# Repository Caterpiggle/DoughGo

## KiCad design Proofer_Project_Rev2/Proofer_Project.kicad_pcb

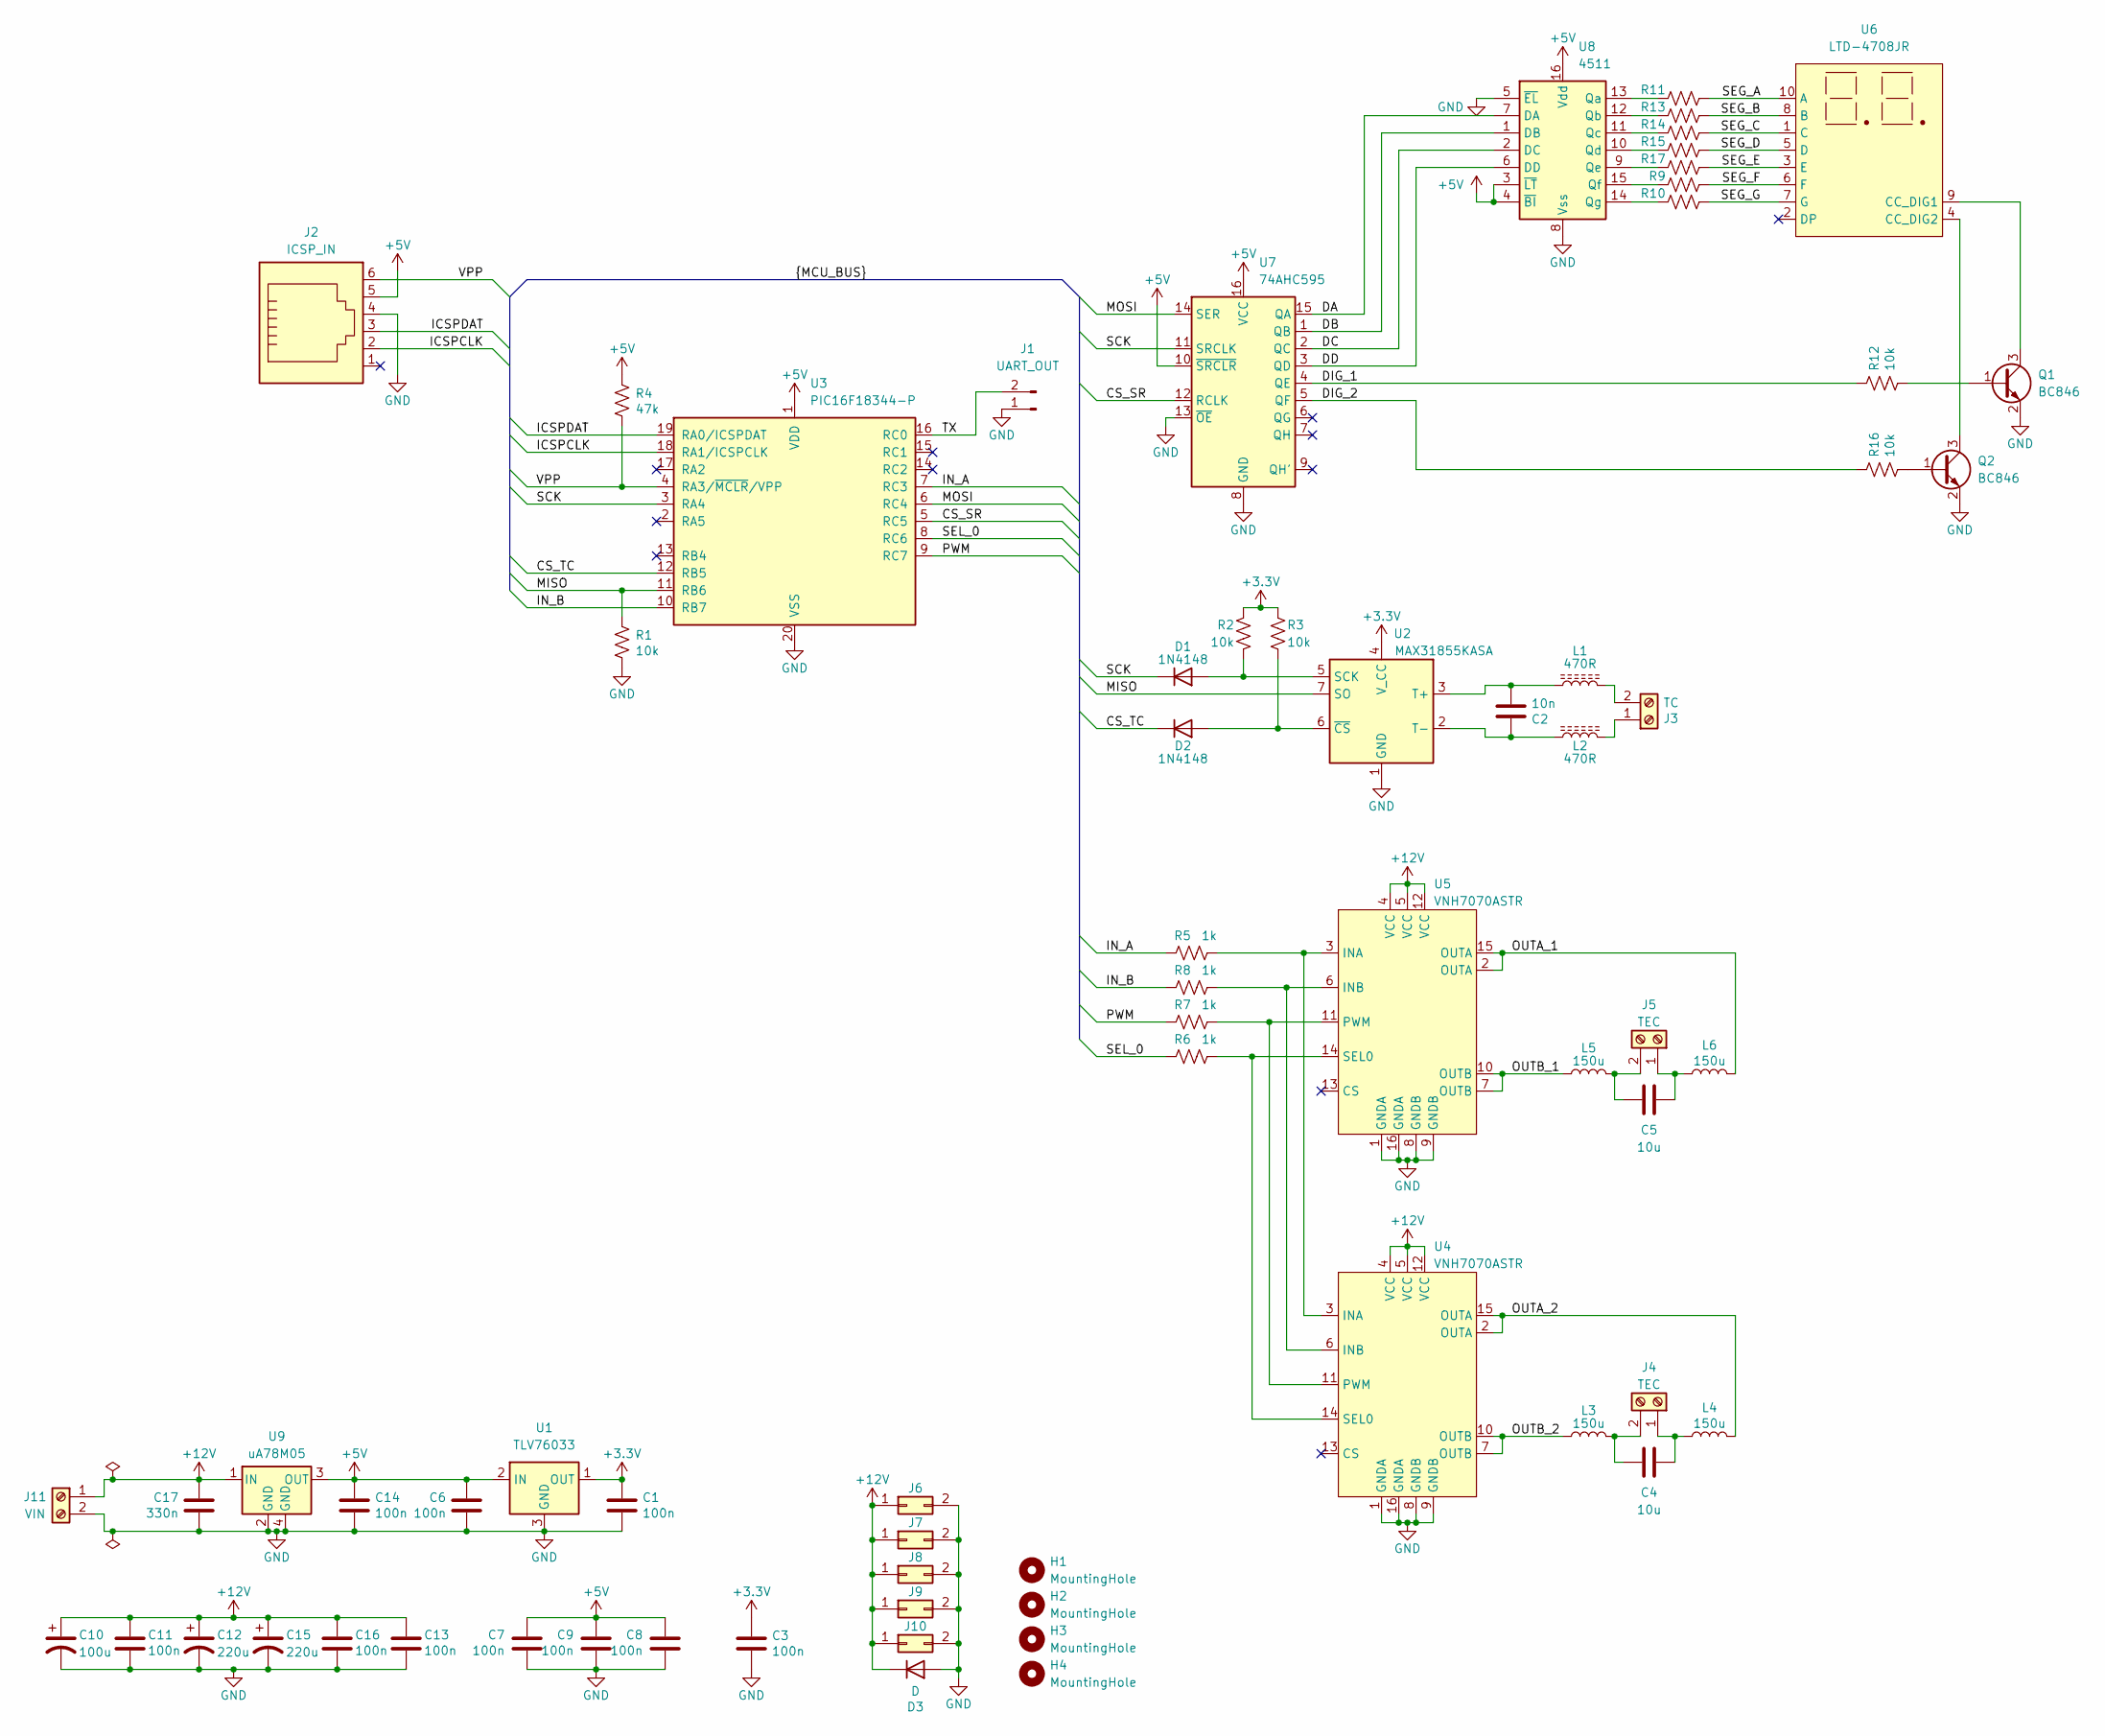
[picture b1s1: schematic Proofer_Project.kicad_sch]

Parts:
C1, C3, C6, C7, C8, C9, C11, C13, C14, C16: 100n; C_0805_2012Metric
C2: 10n; C_0805_2012Metric
C4, C5: 10u; C_Rect_L18.0mm_W9.0mm_P15.00mm_FKS3_FKP3
C10: 100u; CP_Radial_D6.3mm_P2.50mm
C12, C15: 220u; CP_Radial_D6.3mm_P2.50mm
C17: 330n; C_0805_2012Metric
D1, D2: 1N4148; D_SOD-323
D3: D; D_SOD-123
H1, H2, H3, H4: MountingHole; MountingHole_3.2mm_M3
J1: UART_OUT; PinHeader_1x02_P2.54mm_Horizontal
J2: ICSP_IN; RJ11
J3: TC; TerminalBlock_bornier-2_P5.08mm
J4, J5: TEC; TerminalBlock_bornier-2_P5.08mm
J6, J7, J8, J9, J10: Conn_02x01; PinHeader_1x02_P2.54mm_Vertical
J11: VIN; TerminalBlock_bornier-2_P5.08mm
L1, L2: 470R; L_0805_2012Metric
L3, L4, L5, L6: 150u; L_Toroid_Vertical_L26.7mm_W14.0mm_P10.16mm_Pulse_D
Q1, Q2: BC846; SOT-23
R1, R2, R3, R12, R16: 10k; R_0805_2012Metric
R4: 47k; R_0805_2012Metric
R5, R6, R7, R8: 1k; R_0805_2012Metric
R9, R10, R11, R13, R14, R15, R17: R_US; R_0805_2012Metric
U1: TLV76033; SOT-23
U2: MAX31855KASA; SOIC-8_3.9x4.9mm_P1.27mm
U3: PIC16F18344-P; DIP-20_W7.62mm_Socket
U4, U5: VNH7070ASTR; SO-16_3.9x9.9mm_P1.27mm
U6: LTD-4708JR
U7: 74AHC595; SOIC-16_3.9x9.9mm_P1.27mm
U8: 4511; SOIC-16_3.9x9.9mm_P1.27mm
U9: uA78M05; SOT-223

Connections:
+3.3V: C1.1, C3.1, R2.1, R3.1, U1.1 (OUT), U2.4 (V_CC)
+5V: C6.1, C7.1, C8.1, C9.1, C14.1, J2.5, R4.2, U1.2 (IN), U3.1 (VDD), U7.10 (~SRCLR), U7.16 (VCC), U8.3 (~LT), U8.4 (~BI), U8.16 (Vdd), U9.3 (OUT)
+12V: C10.1, C11.1, C12.1, C13.1, C15.1, C16.1, C17.1, D3.1 (K), J6.1, J7.1, J8.1, J9.1, J10.1, J11.1, U4.4 (VCC), U4.5 (VCC), U4.12 (VCC), U5.4 (VCC), U5.5 (VCC), U5.12 (VCC), U9.1 (IN)
/CS_SR: U3.5 (RC5), U7.12 (RCLK)
/CS_TC: D2.1 (K), U3.12 (RB5)
/DA: U7.15 (QA), U8.7 (DA)
/DB: U7.1 (QB), U8.1 (DB)
/DC: U7.2 (QC), U8.2 (DC)
/DD: U7.3 (QD), U8.6 (DD)
/DIG_1: R12.1, U7.4 (QE)
/DIG_2: R16.1, U7.5 (QF)
/ICSPCLK: J2.2, U3.18 (RA1/ICSPCLK)
/ICSPDAT: J2.3, U3.19 (RA0/ICSPDAT)
/IN_A: R5.1, U3.7 (RC3)
/IN_B: R8.1, U3.10 (RB7)
/MISO: R1.2, U2.7 (SO), U3.11 (RB6)
/MOSI: U3.6 (RC4), U7.14 (SER)
/OUTA_1: L6.2, U5.2 (OUTA), U5.15 (OUTA)
/OUTA_2: L4.2, U4.2 (OUTA), U4.15 (OUTA)
/OUTB_1: L5.1, U5.7 (OUTB), U5.10 (OUTB)
/OUTB_2: L3.1, U4.7 (OUTB), U4.10 (OUTB)
/PWM: R7.1, U3.9 (RC7)
/SCK: D1.1 (K), U3.3 (RA4), U7.11 (SRCLK)
/SEG_A: R11.2, U6.10 (A)
/SEG_B: R13.2, U6.8 (B)
/SEG_C: R14.2, U6.1 (C)
/SEG_D: R15.2, U6.5 (D)
/SEG_E: R17.2, U6.3 (E)
/SEG_F: R9.2, U6.6 (F)
/SEG_G: R10.2, U6.7 (G)
/SEL_0: R6.1, U3.8 (RC6)
/TX: J1.2, U3.16 (RC0)
/VPP: J2.6, R4.1, U3.4 (RA3/~MCLR/VPP)
GND: C1.2, C3.2, C6.2, C7.2, C8.2, C9.2, C10.2, C11.2, C12.2, C13.2, C14.2, C15.2, C16.2, C17.2, D3.2 (A), J1.1, J2.4, J6.2, J7.2, J8.2, J9.2, J10.2, J11.2, Q1.2 (E), Q2.2 (E), R1.1, U1.3 (GND), U2.1 (GND), U3.20 (VSS), U4.1 (GNDA), U4.8 (GNDB), U4.9 (GNDB), U4.16 (GNDA), U5.1 (GNDA), U5.8 (GNDB), U5.9 (GNDB), U5.16 (GNDA), U7.8 (GND), U7.13 (~OE), U8.5 (~EL), U8.8 (Vss), U9.2 (GND), U9.4 (GND)
unnamed: D1.2 (A), R2.2, U2.5 (SCK)
unnamed: D2.2 (A), R3.2, U2.6 (~CS)
unnamed: J3.1, L2.2
unnamed: J3.2, L1.2
unnamed: C4.2, J4.1, L4.1
unnamed: C4.1, J4.2, L3.2
unnamed: C5.2, J5.1, L6.1
unnamed: C5.1, J5.2, L5.2
unnamed: Q1.1 (B), R12.2
unnamed: Q1.3 (C), U6.9 (CC_DIG1)
unnamed: Q2.1 (B), R16.2
unnamed: Q2.3 (C), U6.4 (CC_DIG2)
unnamed: C2.2, L1.1, U2.3 (T+)
unnamed: C2.1, L2.1, U2.2 (T-)
unnamed: R5.2, U4.3 (INA), U5.3 (INA)
unnamed: R8.2, U4.6 (INB), U5.6 (INB)
unnamed: R7.2, U4.11 (PWM), U5.11 (PWM)
unnamed: R6.2, U4.14 (SEL0), U5.14 (SEL0)
unnamed: R11.1, U8.13 (Qa)
unnamed: R13.1, U8.12 (Qb)
unnamed: R14.1, U8.11 (Qc)
unnamed: R15.1, U8.10 (Qd)
unnamed: R17.1, U8.9 (Qe)
unnamed: R9.1, U8.15 (Qf)
unnamed: R10.1, U8.14 (Qg)

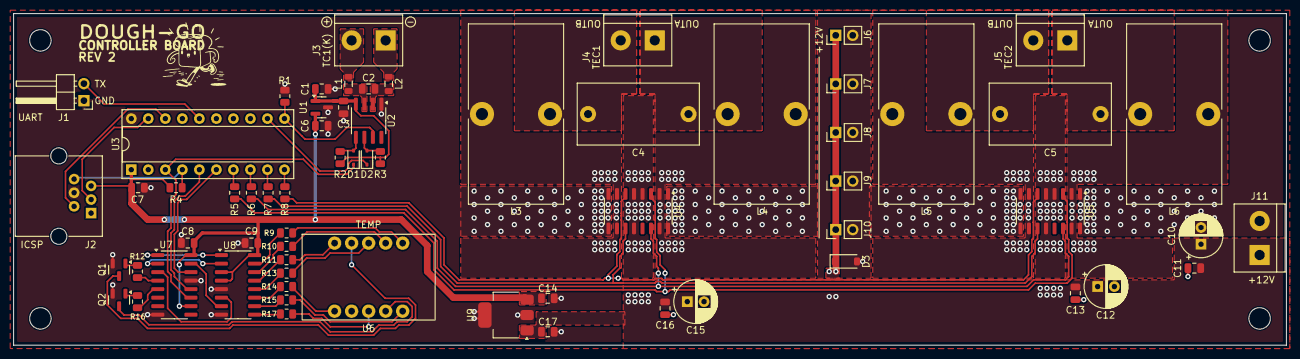
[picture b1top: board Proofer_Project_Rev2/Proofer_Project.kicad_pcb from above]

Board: 2 copper layers, 190.0 x 49.5 mm, 69 parts (0 on the bottom side), 59 nets.

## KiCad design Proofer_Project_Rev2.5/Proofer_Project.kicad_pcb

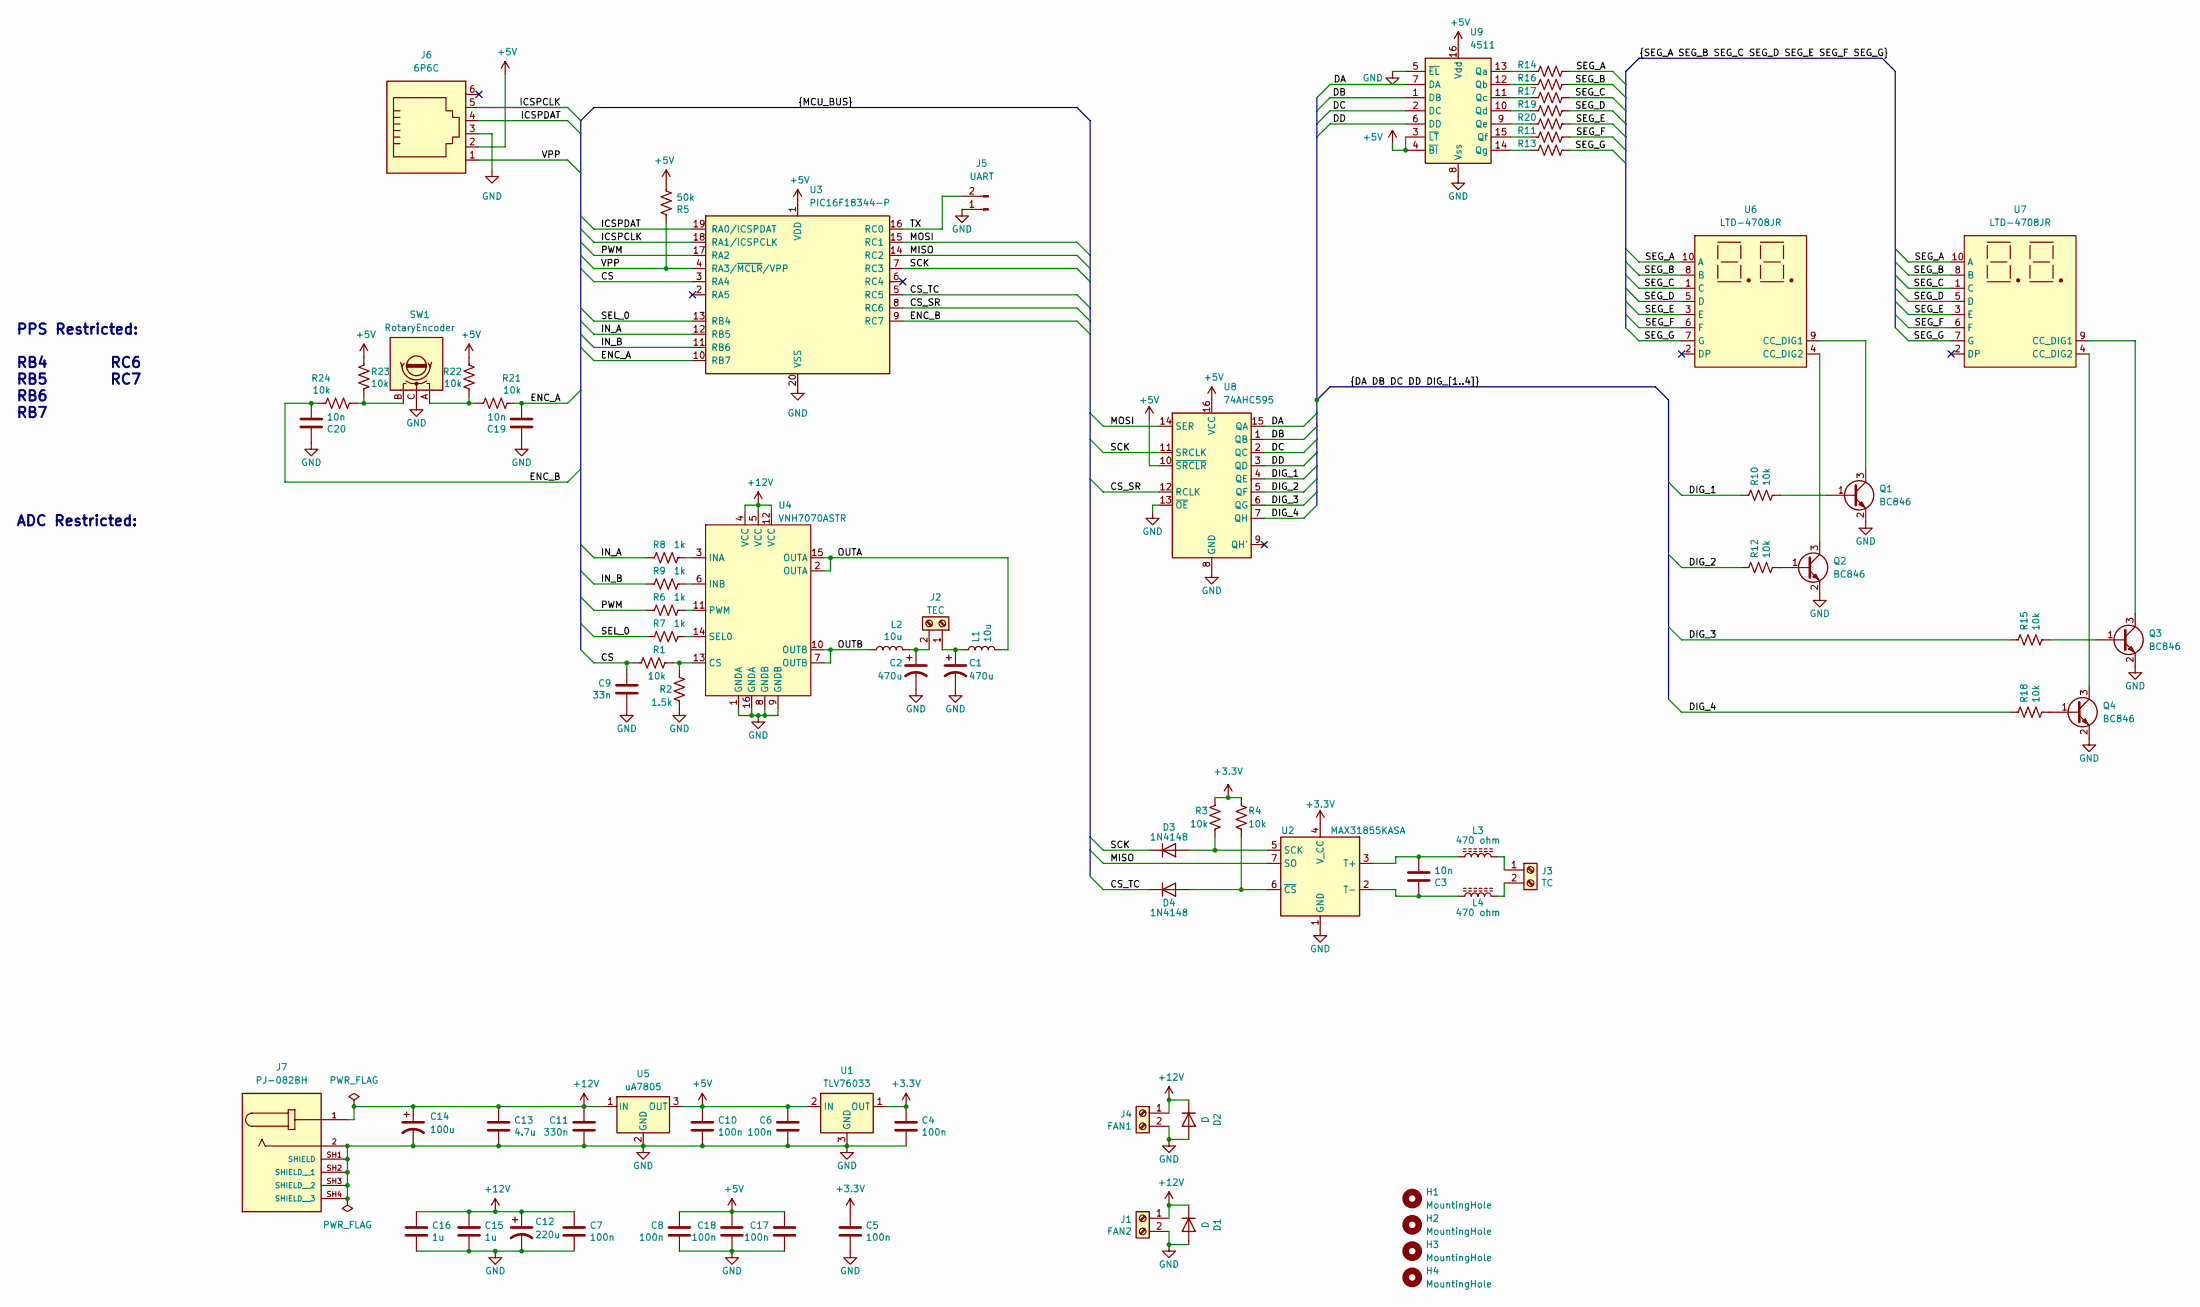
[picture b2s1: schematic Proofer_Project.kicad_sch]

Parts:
C1, C2: 470u; CP_Radial_D10.0mm_P5.00mm
C3, C19, C20: 10n; C_0805_2012Metric
C4, C5, C6, C7, C8, C10, C17, C18: 100n; C_0805_2012Metric
C9: 33n; C_0805_2012Metric
C11: 330n; C_0805_2012Metric
C12: 220u; CP_Radial_D5.0mm_P2.00mm
C13: 4.7u; C_0805_2012Metric
C14: 100u; CP_Radial_D5.0mm_P2.00mm
C15, C16: 1u; C_0805_2012Metric
D1, D2: D; D_SOD-123
D3, D4: 1N4148; D_SOD-323
H1, H2, H3, H4: MountingHole; MountingHole_3.2mm_M3
J1: FAN2; TerminalBlock_bornier-2_P5.08mm
J2: TEC; TerminalBlock_bornier-2_P5.08mm
J3: TC; PCC-SMP
J4: FAN1; TerminalBlock_bornier-2_P5.08mm
J5: UART; PinHeader_1x02_P2.54mm_Horizontal
J6: 6P6C; RJ11
J7: PJ-082BH; CUI_PJ-082BH; PARTREV 1.04
L1, L2: 10u; L_Radial_D24.4mm_P23.90mm_Murata_1400series
L3, L4: 470 ohm; L_0805_2012Metric
Q1, Q2, Q3, Q4: BC846; SOT-23
R1, R3, R4, R10, R12, R15, R18, R21, R22, R23, R24: 10k; R_0805_2012Metric
R2: 1.5k; R_0805_2012Metric
R5: 50k; R_0805_2012Metric
R6, R7, R8, R9: 1k; R_0805_2012Metric
R11, R13, R14, R16, R17, R19, R20: R_US; R_0805_2012Metric
SW1: RotaryEncoder; RotaryEncoder_Alps_EC11E-Switch_Vertical_H20mm
U1: TLV76033; SOT-23
U2: MAX31855KASA; SOIC-8_3.9x4.9mm_P1.27mm
U3: PIC16F18344-P; DIP-20_W7.62mm_Socket
U4: VNH7070ASTR; SO-16_3.9x9.9mm_P1.27mm
U5: uA7805; SOT-223
U6, U7: LTD-4708JR
U8: 74AHC595; SOIC-16_3.9x9.9mm_P1.27mm
U9: 4511; SOIC-16_3.9x9.9mm_P1.27mm

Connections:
+3.3V: C4.1, C5.1, R3.1, R4.1, U1.1 (OUT), U2.4 (V_CC)
+5V: C6.1, C8.1, C10.1, C17.1, C18.1, J6.2, R5.2, R22.2, R23.2, U1.2 (IN), U3.1 (VDD), U5.3 (OUT), U8.10 (~SRCLR), U8.16 (VCC), U9.3 (~LT), U9.4 (~BI), U9.16 (Vdd)
+12V: C7.1, C11.1, C12.1, C13.1, C14.1, C15.1, C16.1, D1.1 (K), D2.1 (K), J1.1, J4.1, J7.1, U4.4 (VCC), U4.5 (VCC), U4.12 (VCC), U5.1 (IN)
/CS: C9.1, R1.1, U3.3 (RA4)
/CS_SR: U3.8 (RC6), U8.12 (RCLK)
/CS_TC: D4.1 (K), U3.5 (RC5)
/DA: U8.15 (QA), U9.7 (DA)
/DB: U8.1 (QB), U9.1 (DB)
/DC: U8.2 (QC), U9.2 (DC)
/DD: U8.3 (QD), U9.6 (DD)
/DIG_1: R10.1, U8.4 (QE)
/DIG_2: R12.1, U8.5 (QF)
/DIG_3: R15.1, U8.6 (QG)
/DIG_4: R18.1, U8.7 (QH)
/ENC_A: C19.2, R21.2, U3.10 (RB7)
/ENC_B: C20.2, R24.1, U3.9 (RC7)
/ICSPCLK: J6.5, U3.18 (RA1/ICSPCLK)
/ICSPDAT: J6.4, U3.19 (RA0/ICSPDAT)
/IN_A: R8.1, U3.12 (RB5)
/IN_B: R9.1, U3.11 (RB6)
/MISO: U2.7 (SO), U3.14 (RC2)
/MOSI: U3.15 (RC1), U8.14 (SER)
/OUTA: L1.2, U4.2 (OUTA), U4.15 (OUTA)
/OUTB: L2.1, U4.7 (OUTB), U4.10 (OUTB)
/PWM: R6.1, U3.17 (RA2)
/SCK: D3.1 (K), U3.7 (RC3), U8.11 (SRCLK)
/SEG_A: R14.2, U6.10 (A), U7.10 (A)
/SEG_B: R16.2, U6.8 (B), U7.8 (B)
/SEG_C: R17.2, U6.1 (C), U7.1 (C)
/SEG_D: R19.2, U6.5 (D), U7.5 (D)
/SEG_E: R20.2, U6.3 (E), U7.3 (E)
/SEG_F: R11.2, U6.6 (F), U7.6 (F)
/SEG_G: R13.2, U6.7 (G), U7.7 (G)
/SEL_0: R7.1, U3.13 (RB4)
/TX: J5.2, U3.16 (RC0)
/VPP: J6.1, R5.1, U3.4 (RA3/~MCLR/VPP)
GND: C1.2, C2.2, C4.2, C5.2, C6.2, C7.2, C8.2, C9.2, C10.2, C11.2, C12.2, C13.2, C14.2, C15.2, C16.2, C17.2, C18.2, C19.1, C20.1, D1.2 (A), D2.2 (A), J1.2, J4.2, J5.1, J6.3, J7.2, J7.SH1 (SHIELD), J7.SH2 (SHIELD__1), J7.SH3 (SHIELD__2), J7.SH4 (SHIELD__3), Q1.2 (E), Q2.2 (E), Q3.2 (E), Q4.2 (E), R2.1, SW1.C, U1.3 (GND), U2.1 (GND), U3.20 (VSS), U4.1 (GNDA), U4.8 (GNDB), U4.9 (GNDB), U4.16 (GNDA), U5.2 (GND), U8.8 (GND), U8.13 (~OE), U9.5 (~EL), U9.8 (Vss)
unnamed: D3.2 (A), R3.2, U2.5 (SCK)
unnamed: D4.2 (A), R4.2, U2.6 (~CS)
unnamed: C1.1, J2.1, L1.1
unnamed: C2.1, J2.2, L2.2
unnamed: J3.1, L3.2
unnamed: J3.2, L4.2
unnamed: Q1.1 (B), R10.2
unnamed: Q1.3 (C), U6.9 (CC_DIG1)
unnamed: Q2.1 (B), R12.2
unnamed: Q2.3 (C), U6.4 (CC_DIG2)
unnamed: Q3.1 (B), R15.2
unnamed: Q3.3 (C), U7.9 (CC_DIG1)
unnamed: Q4.1 (B), R18.2
unnamed: Q4.3 (C), U7.4 (CC_DIG2)
unnamed: R21.1, R22.1, SW1.A
unnamed: R23.1, R24.2, SW1.B
unnamed: C3.2, L3.1, U2.3 (T+)
unnamed: C3.1, L4.1, U2.2 (T-)
unnamed: R1.2, R2.2, U4.13 (CS)
unnamed: R8.2, U4.3 (INA)
unnamed: R9.2, U4.6 (INB)
unnamed: R6.2, U4.11 (PWM)
unnamed: R7.2, U4.14 (SEL0)
unnamed: R14.1, U9.13 (Qa)
unnamed: R16.1, U9.12 (Qb)
unnamed: R17.1, U9.11 (Qc)
unnamed: R19.1, U9.10 (Qd)
unnamed: R20.1, U9.9 (Qe)
unnamed: R11.1, U9.15 (Qf)
unnamed: R13.1, U9.14 (Qg)

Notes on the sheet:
ADC Restricted:
PPS Restricted: RB4 RC6 RB5 RC7 RB6 RB7

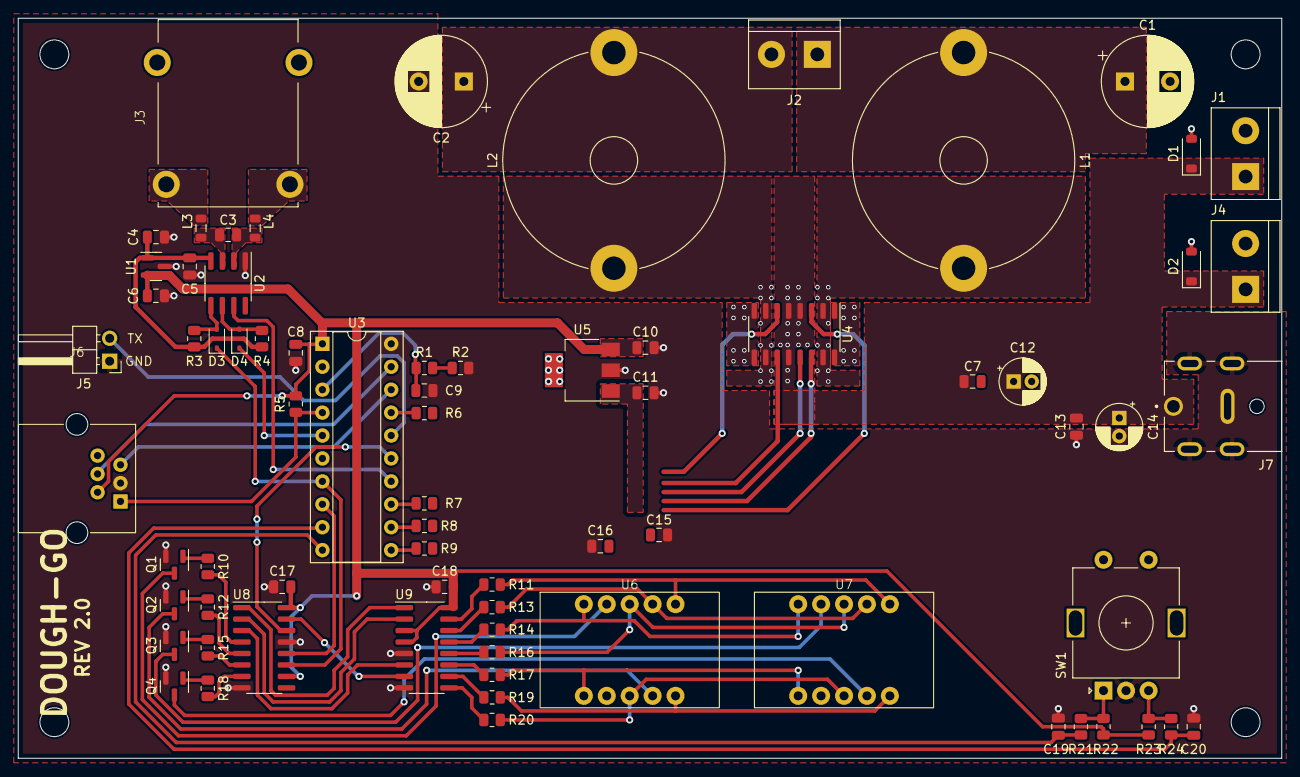
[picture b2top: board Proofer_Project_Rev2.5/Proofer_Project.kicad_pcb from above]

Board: 2 copper layers, 140.0 x 82.0 mm, 77 parts (0 on the bottom side), 67 nets.

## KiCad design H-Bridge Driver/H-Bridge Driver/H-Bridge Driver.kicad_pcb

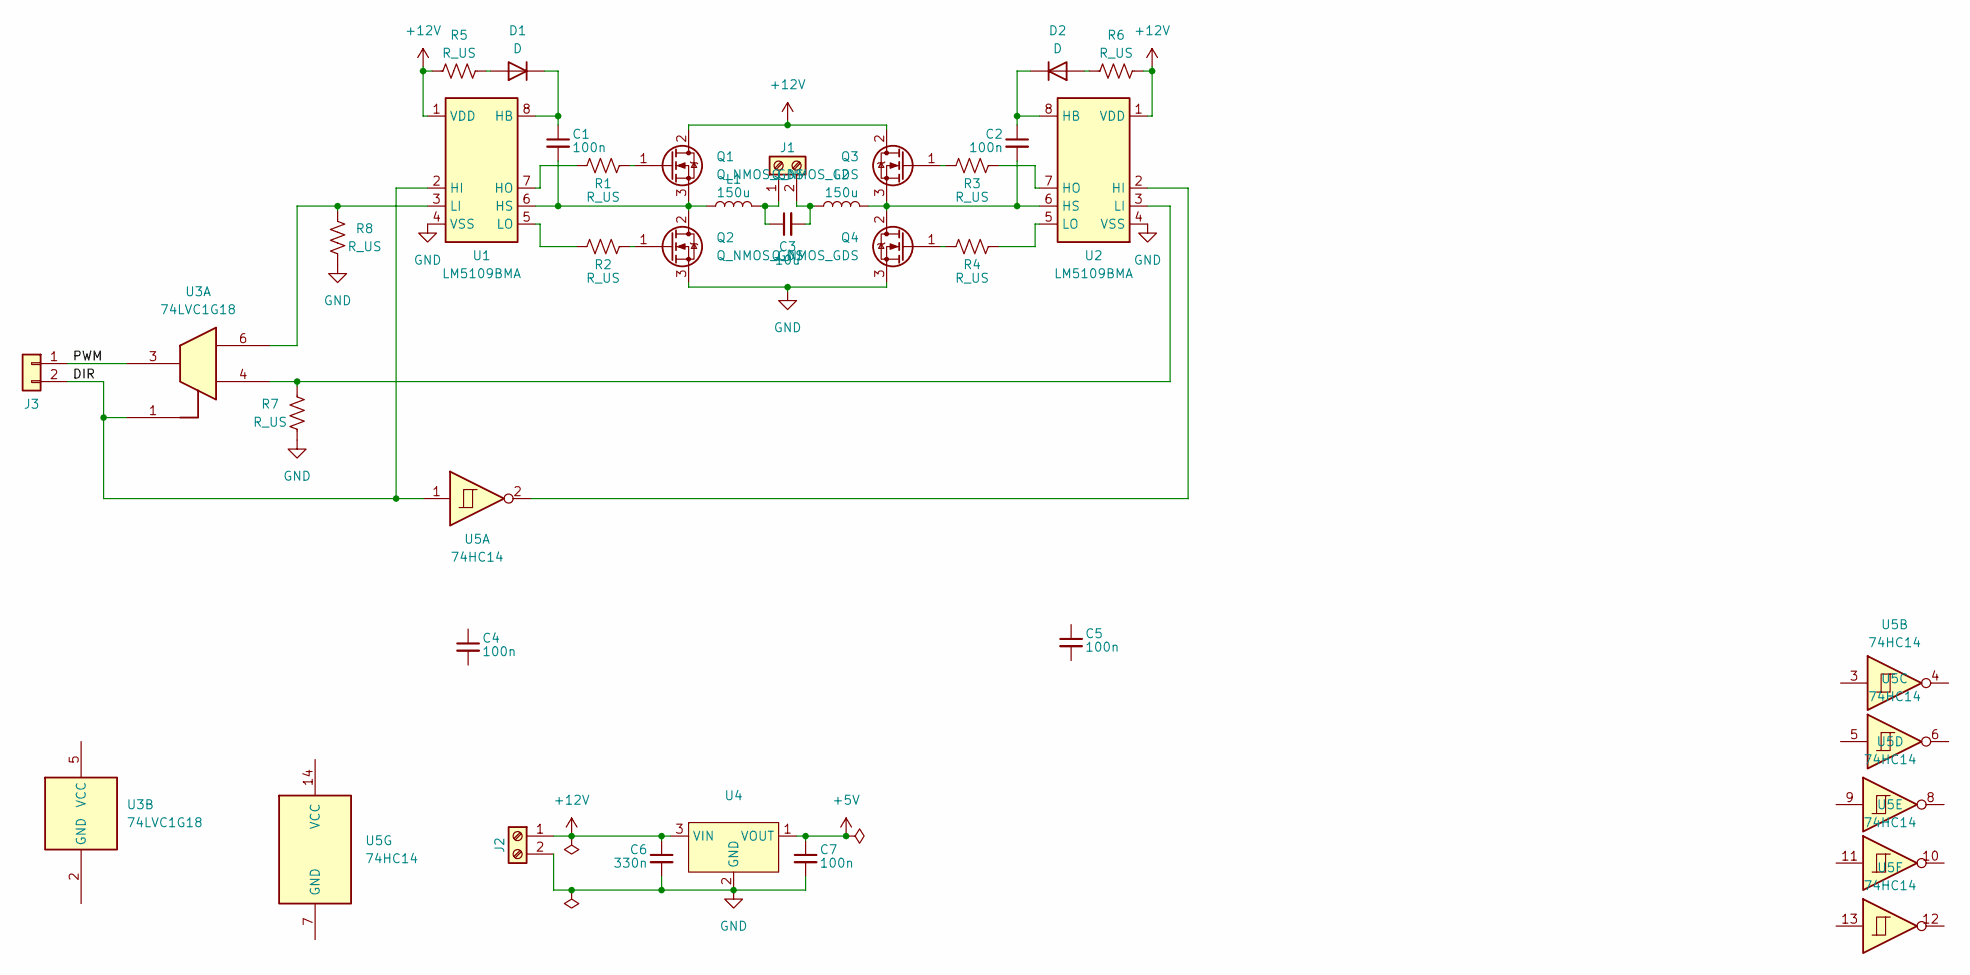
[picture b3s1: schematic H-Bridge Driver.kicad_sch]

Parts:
C1, C2, C4, C5, C7: 100n; C_0805_2012Metric
C3: 10u; C_Rect_L18.0mm_W9.0mm_P15.00mm_FKS3_FKP3
C6: 330n; C_0805_2012Metric
D1, D2: D; D_SOD-323
J1, J2: Screw_Terminal_01x02; TerminalBlock_bornier-2_P5.08mm
J3: Conn_01x02; PinHeader_1x02_P2.54mm_Vertical
L1, L2: 150u; L_Toroid_Vertical_L26.7mm_W14.0mm_P10.16mm_Pulse_D
Q1, Q2, Q3, Q4: Q_NMOS_GDS; TO-252-2
R1, R2, R3, R4, R5, R6, R7, R8: R_US; R_0805_2012Metric
U1, U2: LM5109BMA; SOIC-8_3.9x4.9mm_P1.27mm
U3: 74LVC1G18; SOT-23-6
U4: SOT-89-3
U5: 74HC14

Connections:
+5V: C7.1, U4.1 (VOUT)
+12V: C6.1, J2.1, Q1.2 (D), Q3.2 (D), R5.1, R6.2, U1.1 (VDD), U2.1 (VDD), U4.3 (VIN)
/DIR: J3.2, U1.2 (HI), U3.1, U5.1
/PWM: J3.1, U3.3
GND: C6.2, C7.2, J2.2, Q2.3 (S), Q4.3 (S), R7.1, R8.1, U1.4 (VSS), U2.4 (VSS), U4.2 (GND)
unnamed: D1.2 (A), R5.2
unnamed: C1.1, D1.1 (K), U1.8 (HB)
unnamed: D2.2 (A), R6.1
unnamed: C2.1, D2.1 (K), U2.8 (HB)
unnamed: C3.1, J1.1, L1.2
unnamed: C3.2, J1.2, L2.1
unnamed: Q1.1 (G), R1.2
unnamed: C1.2, L1.1, Q1.3 (S), Q2.2 (D), U1.6 (HS)
unnamed: Q2.1 (G), R2.2
unnamed: Q3.1 (G), R3.1
unnamed: C2.2, L2.2, Q3.3 (S), Q4.2 (D), U2.6 (HS)
unnamed: Q4.1 (G), R4.1
unnamed: R1.1, U1.7 (HO)
unnamed: R8.2, U1.3 (LI), U3.6
unnamed: R2.1, U1.5 (LO)
unnamed: U2.2 (HI), U5.2
unnamed: R3.2, U2.7 (HO)
unnamed: R7.2, U2.3 (LI), U3.4
unnamed: R4.2, U2.5 (LO)

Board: 2 copper layers, 30 parts (0 on the bottom side), 23 nets, no tracks yet.

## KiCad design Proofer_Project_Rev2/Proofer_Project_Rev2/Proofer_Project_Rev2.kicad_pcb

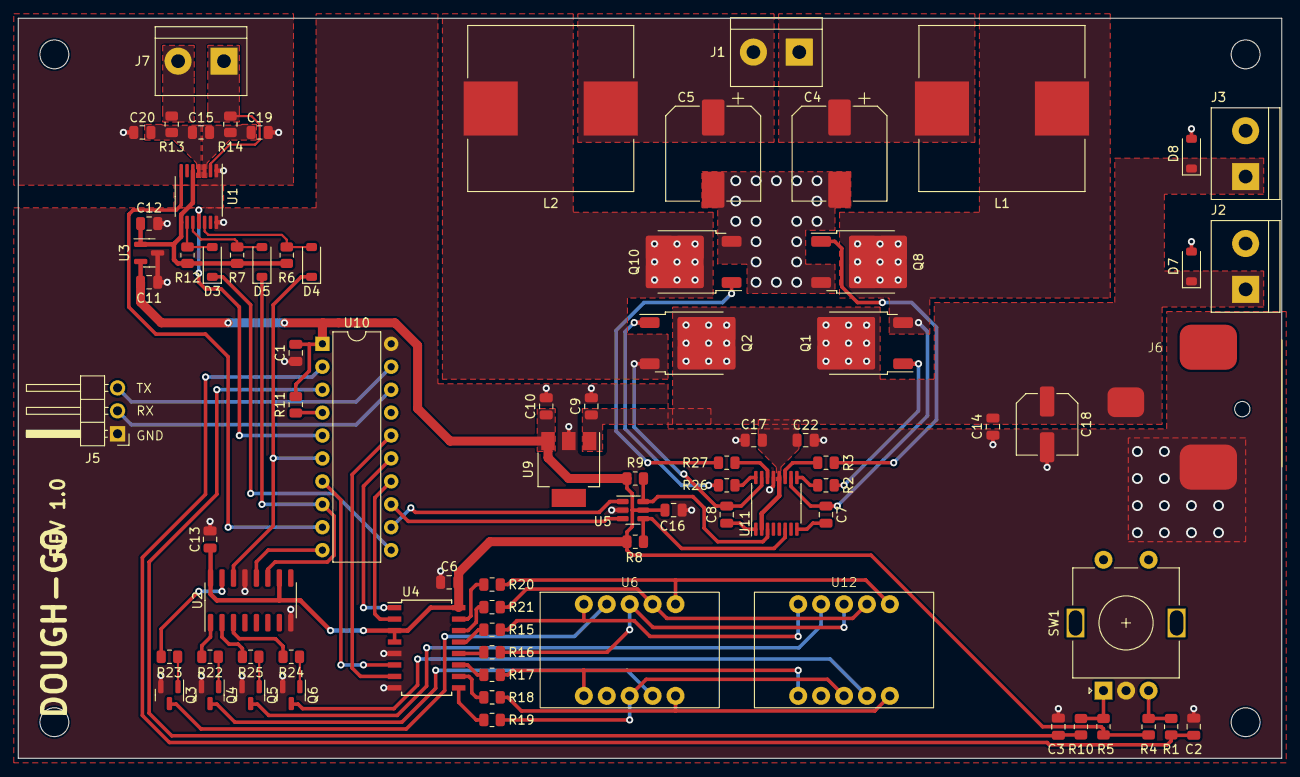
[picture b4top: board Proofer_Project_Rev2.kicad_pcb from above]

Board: 2 copper layers, 140.0 x 82.0 mm, 84 parts (0 on the bottom side), 72 nets.

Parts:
C1, C6, C10, C11, C12, C13, C15, C16: 100n; C_0805_2012Metric
C2, C3, C19, C20: 10n; C_0805_2012Metric
C4, C5: 470u; CP_Elec_10x10
C7, C8, C17, C22: 1u; C_0805_2012Metric
C9: 330n; C_0805_2012Metric
C14: 4.7u; C_0805_2012Metric
C18: 100u; C_Elec_6.3x5.4
D3, D4, D5, D7, D8: D; D_SOD-123
H1, H2, H3, H4: MountingHole; MountingHole_3.2mm_M3
J1: TEC; TerminalBlock_bornier-2_P5.08mm
J2: FAN1; TerminalBlock_bornier-2_P5.08mm
J3: FAN2; TerminalBlock_bornier-2_P5.08mm
J5: UART; PinHeader_1x03_P2.54mm_Horizontal
J6: Barrel_Jack_Switch; RASM10PS
J7: TC; TerminalBlock_bornier-2_P5.08mm
L1, L2: 10u; L_Wuerth_HCI-1890
Q1, Q2, Q8, Q10: Q_NMOS_GDS; TO-252-2
Q3, Q4, Q5, Q6: BC846; SOT-23
R1, R4, R5, R6, R7, R8, R9, R10, R11, R12, R22, R23, R24, R25: 10k; R_0805_2012Metric
R2, R26: 10R; R_0805_2012Metric
R3, R27: 2R; R_0805_2012Metric
R13, R14: 100R; R_0805_2012Metric
R15, R16, R17, R18, R19, R20, R21: R_US; R_0805_2012Metric
SW1: Rotary_Encoder; RotaryEncoder_Alps_EC11E-Switch_Vertical_H20mm
U1: MAX31856; TSSOP-14_4.4x5mm_P0.65mm
U2: 74AHC595; SOIC-16_3.9x9.9mm_P1.27mm
U3: TLV76033; SOT-23
U4: 4511; SOIC-16W_5.3x10.2mm_P1.27mm
U5: 74LVC1G18; SOT-23-6
U6, U12: LTD-4708JR
U9: uA7805; SOT-223
U10: PIC16F18344-P; DIP-20_W7.62mm
U11: MIC4606-2; TSSOP-16_4.4x5mm_P0.65mm

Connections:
+3.3V: C12.1, R6.1, R7.1, R12.1, U1.5 (AVDD), U1.8 (DVDD), U3.1 (OUT)
+5V: C1.1, C6.1, C10.1, C11.1, C13.1, C16.1, R4.2, R5.2, R8.2, R9.1, R11.2, U2.10 (~SRCLR), U2.16 (VCC), U3.2 (IN), U4.3 (~LT), U4.4 (~BI), U4.16 (Vdd), U5.5 (VCC), U9.3 (OUT), U10.1 (VDD)
+12V: C9.1, C14.1, C17.1, C18.1, C22.1, D7.1 (K), D8.1 (K), J2.1, J3.1, J6.1, Q1.2 (D), Q2.2 (D), U9.1 (IN), U11.2 (EN), U11.12 (VDD)
/CS_SR: U2.12 (RCLK), U10.10 (RB7)
/CS_TC: D3.1 (K), U10.11 (RB6)
/DEC_A: U4.7 (DA), U10.16 (RC0)
/DEC_B: U4.1 (DB), U10.15 (RC1)
/DEC_C: U4.2 (DC), U10.14 (RC2)
/DEC_D: U4.6 (DD), U10.7 (RC3)
/DIR_SEL: U5.1, U10.12 (RB5)
/DRDY: U1.7 (~DRDY), U10.9 (RC7)
/ENC_A: C3.2, R10.2, U10.3 (RA4)
/ENC_B: C2.2, R1.1, U10.2 (RA5)
/MISO: U1.11 (SDO), U10.5 (RC5)
/MOSI: D4.1 (K), U2.14 (SER), U10.6 (RC4)
/PWM: U5.3, U10.13 (RB4)
/RX: J5.2, U10.18 (RA1/ICSPCLK)
/SCK: D5.1 (K), U2.11 (SRCLK), U10.8 (RC6)
/TX: J5.3, U10.19 (RA0/ICSPDAT)
GNDA: C1.2, C2.1, C3.1, C4.2, C5.2, C6.2, C9.2, C10.2, C11.2, C12.2, C13.2, C14.2, C16.2, C17.2, C18.2, C19.1, C20.1, C22.2, D7.2 (A), D8.2 (A), J2.2, J3.2, J5.1, J6.2, Q3.2 (E), Q4.2 (E), Q5.2 (E), Q6.2 (E), Q8.3 (S), Q10.3 (S), SW1.C, U1.1 (AGND), U1.14 (DGND), U2.8 (GND), U2.13 (~OE), U3.3 (GND), U4.5 (~EL), U4.8 (Vss), U5.2 (GND), U9.2 (GND), U10.20 (VSS), U11.13 (VSS)
unnamed: D3.2 (A), R12.2, U1.9 (~CS)
unnamed: D4.2 (A), R6.2, U1.12 (SDI)
unnamed: D5.2 (A), R7.2, U1.10 (SCK)
unnamed: C4.1, J1.1, L1.2
unnamed: C5.1, J1.2, L2.1
unnamed: J7.1, R14.1, U1.2 (BIAS)
unnamed: J7.2, R13.1
unnamed: Q1.1 (G), R2.2
unnamed: C7.1, L1.1, Q1.3 (S), Q8.2 (D), U11.10 (AHS)
unnamed: Q2.1 (G), R26.1
unnamed: Q3.1 (B), R23.2
unnamed: Q3.3 (C), U6.9 (CC_DIG1)
unnamed: Q4.1 (B), R22.2
unnamed: Q4.3 (C), U6.4 (CC_DIG2)
unnamed: Q5.1 (B), R25.2
unnamed: Q5.3 (C), U12.9 (CC_DIG1)
unnamed: Q6.1 (B), R24.2
unnamed: Q6.3 (C), U12.4 (CC_DIG2)
unnamed: Q8.1 (G), R3.2
unnamed: C8.2, L2.2, Q2.3 (S), Q10.2 (D), U11.15 (BHS)
unnamed: Q10.1 (G), R27.1
unnamed: R1.2, R4.1, SW1.B
unnamed: R5.1, R10.1, SW1.A
unnamed: C15.2, C20.2, R13.2, U1.4 (T+)
unnamed: C15.1, C19.2, R14.2, U1.3 (T-)
unnamed: R23.1, U2.15 (QA)
unnamed: R22.1, U2.1 (QB)
unnamed: R25.1, U2.2 (QC)
unnamed: R24.1, U2.3 (QD)
unnamed: R15.1, U4.13 (Qa)
unnamed: R16.1, U4.12 (Qb)
unnamed: R17.1, U4.11 (Qc)
unnamed: R18.1, U4.10 (Qd)
unnamed: R19.1, U4.9 (Qe)
unnamed: R20.1, U4.15 (Qf)
unnamed: R21.1, U4.14 (Qg)
unnamed: R11.1, U10.4 (RA3/~MCLR/VPP)
unnamed: C7.2, U11.8 (AHB)
unnamed: R2.1, U11.9 (AHO)
unnamed: R3.1, U11.11 (ALO)
unnamed: R8.1, U5.4, U11.6 (APWM)
unnamed: C8.1, U11.1 (BHB)
unnamed: R26.2, U11.16 (BHO)
unnamed: R27.2, U11.14 (BLO)
unnamed: R9.2, U5.6, U11.3 (BPWM)
unnamed: R15.2, U6.10 (A), U12.10 (A)
unnamed: R16.2, U6.8 (B), U12.8 (B)
unnamed: R17.2, U6.1 (C), U12.1 (C)
unnamed: R18.2, U6.5 (D), U12.5 (D)
unnamed: R19.2, U6.3 (E), U12.3 (E)
unnamed: R20.2, U6.6 (F), U12.6 (F)
unnamed: R21.2, U6.7 (G), U12.7 (G)

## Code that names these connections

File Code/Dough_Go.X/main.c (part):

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#pragma config FCMEN = ON       // Fail-Safe Clock Monitor Enable (Fail-Safe Clock Monitor is enabled)

// CONFIG2
#pragma config MCLRE = ON       // Master Clear Enable bit (MCLR/VPP pin function is MCLR; Weak pull-up enabled)
#pragma config PWRTE = OFF      // Power-up Timer Enable bit (PWRT disabled)
#pragma config WDTE = OFF       // Watchdog Timer Enable bits (WDT disabled; SWDTEN is ignored)
#pragma config LPBOREN = OFF    // Low-power BOR enable bit (ULPBOR disabled)
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#pragma config CPD = OFF        // Data NVM Memory Code Protection bit (Data NVM code protection disabled)

// Pin Definitions
#define	TX  	PORTAbits.RA0   // UART TX output
#define	RX  	PORTAbits.RA1   // UART RX input
#define	ENC_A	PORTAbits.RA4   // Encoder A input
#define	ENC_B	PORTAbits.RA5   // Encoder B input

#define PWM     PORTBbits.RB4   // Peltier driver PWM output
#define DIR_SEL PORTBbits.RB5   // Peltier driver direction selection output
#define CS_TC   PORTBbits.RB6   // Thermocouple chip select output
#define RCLK    PORTBbits.RB7   // Shift register latch output

#define DEC_A   PORTCbits.RC0   // Display decoder bit 0 output
#define DEC_B   PORTCbits.RC1   // Display decoder bit 1 output
#define DEC_C   PORTCbits.RC2   // Display decoder bit 2 output
#define DEC_D   PORTCbits.RC3   // Display decoder bit 3 output
#define MOSI    PORTCbits.RC4   // SPI MOSI output
#define MISO    PORTCbits.RC5   // SPI MISO input
#define SCK     PORTCbits.RC6   // SPI clock output
#define DRDY    PORTCbits.RC7   // TC Data ready input

#define T_MAX   85
#define T_MIN   70
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    uint8_t TC_MB;
    uint8_t TC_LB;
    
    CS_TC = 0;
    TC_HB = SPI_read(0x0C); // LTCBH=
    CS_TC = 1;
    
    CS_TC = 0;
    TC_MB = SPI_read(0x0D); // LTCBH
    CS_TC = 1;
    
    
    CS_TC = 0;
    TC_LB = SPI_read(0x0E); // LTCBH
    CS_TC = 1;
    
    //int temp = ((TC_HB << 16) + (TC_MB << 8) + TC_LB)*1600/6553600;
    T_cur = TC_MB;
}

void get_cur_temp(void) {
    CS_TC = 0;
    SPI_out(0x00);  // CR0
    SPI_out(0x40);  // Set 1SHOT bit
    CS_TC = 1;      // Trigger conversion
    
    while (DRDY);
    
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
    // Initiate ports
    PORTA = 0x00;
    PORTB = 0x40; // RB6 = 1
    PORTC = 0x00;
    
    // Clear data latches
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    //IOCAPbits.IOCAP5 = 1;
    
    // Setup TC converter IC
    //CS_TC = 0;
    //SPI_out(0x80);  // Write - CR0
    //SPI_out(0x80);  // CR0 value
    //CS_TC = 1;
    
    //CS_TC = 0;
    
    //while (1) {
    //    char_print(SPI_read(0x00));
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    
    RCLK  = 0;
    
    PORTCbits.RC0 = 0;	
    PORTCbits.RC1 = 0;	
    PORTCbits.RC2 = 0;	
    PORTCbits.RC3 = 0;
    
    // Enable interrupts
    PIE0bits.IOCIE  = 1;
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
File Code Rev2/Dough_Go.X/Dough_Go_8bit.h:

//=====================================================
//
// Dough-Go Rev 2
// 2024
//
// PIC16F18344
//
//              -----------------
//      VDD  --|  1           20 |--  VSS
//        x  --|  2/RA5   RA0/19 |--  ICSPDAT
//      SCK  --|  3/RA4   RA1/18 |--  ICSPCLK
//      VPP  --|  4/RA3   RA2/17 |--  x
//    CS_SR  --|  5/RC5   RC0/16 |--  UART TX
//     MOSI  --|  6/RC4   RC1/15 |--  x
//     IN_A  --|  7/RC3   RC2/14 |--  X
//    SEL_0  --|  8/RC6   RB4/13 |--  x
//      PWM  --|  9/RC7   RB5/12 |--  CS_TC
//     IN_B  --| 10/RB7   RB6/11 |--  MISO
//              -----------------
//
//=====================================================

// This is a guard condition so that contents of this file are not included
// more than once.  
#ifndef DOUGH_GO_8BIT_H
#define	DOUGH_GO_8BIT_H

#include <xc.h> // include processor files - each processor file is guarded.  
#include <stdint.h>


// CONFIG1
#pragma config FEXTOSC  = OFF     // FEXTOSC External Oscillator mode Selection bits (Oscillator not enabled)
#pragma config RSTOSC   = HFINT1  // Power-up default value for COSC bits (HFINTOSC (1MHz)
#pragma config CLKOUTEN = OFF     // Clock Out Enable bit (CLKOUT function is disabled; I/O or oscillator function on OSC2)
#pragma config CSWEN    = ON      // Clock Switch Enable bit (Writing to NOSC and NDIV is allowed)
#pragma config FCMEN    = ON      // Fail-Safe Clock Monitor Enable (Fail-Safe Clock Monitor is enabled)

// CONFIG2
#pragma config MCLRE    = ON      // Master Clear Enable bit (MCLR/VPP pin function is MCLR; Weak pull-up enabled)
#pragma config PWRTE    = OFF     // Power-up Timer Enable bit (PWRT disabled)
#pragma config WDTE     = OFF     // Watchdog Timer Enable bits (WDT disabled; SWDTEN is ignored)
#pragma config LPBOREN  = OFF     // Low-power BOR enable bit (ULPBOR disabled)
#pragma config BOREN    = OFF     // Brown-out Reset Enable bits (Brown-out Reset disabled)
#pragma config BORV     = LOW     // Brown-out Reset Voltage selection bit (Brown-out voltage (Vbor) set to 2.45V)
#pragma config PPS1WAY  = ON      // PPSLOCK bit One-Way Set Enable bit (The PPSLOCK bit can be cleared and set only once; PPS registers remain locked after one clear/set cycle)
#pragma config STVREN   = ON      // Stack Overflow/Underflow Reset Enable bit (Stack Overflow or Underflow will cause a Reset)
#pragma config DEBUG    = OFF     // Debugger enable bit (Background debugger disabled)

// CONFIG3
#pragma config WRT = OFF // User NVM self-write protection bits (Write protection off)
#pragma config LVP = OFF // Low Voltage Programming Enable bit (High Voltage on MCLR/VPP must be used for programming.)

// CONFIG4
#pragma config CP  = OFF // User NVM Program Memory Code Protection bit (User NVM code protection disabled)
#pragma config CPD = OFF // Data NVM Memory Code Protection bit (Data NVM code protection disabled)

// Pin Definitions
#define CS_TC LATBbits.LATB5 // Thermocouple chip select output
#define CS_SR LATCbits.LATC5 // Display shift register chip select output
#define IN_A  LATCbits.LATC3 // TEC driver IN_A logic input
#define IN_B  LATBbits.LATB7 // TEC driver IN_B logic input
#define SEL_0 LATCbits.LATC6 // TEC driver SEL_0 logic input

#define TSET    24 // Set temp 24C = 75F
#define K_p   0.05 // PID controller constants
#define K_i      0
#define dt    0.13 // dt val (s) based on TC read rate (7.65Hz)

#define N_buff 20 // Size of circular temperature data buffer

uint16_t temp_buffer[N_buff];

uint8_t buff_index = 0;
uint8_t buff_full = 0;

uint8_t SP_crossed = 0; // Setpoint crossing detection for integrator windup

float cur_PWM; // PWM value storage
float PWM_max; // PWM value limit

float cur_temp;

uint8_t TEMPF_ones = 0x20; // Temp disp ones digit, reset 0-on
uint8_t TEMPF_tens = 0x10; // Temp disp tens digit, reset 0-on

uint8_t temp_val = 0;
uint8_t temp_div = 0;

uint8_t mode;

float cum_err     = 0; // Cumulative (integral) error
float cum_err_max = 2; // Max cumulative error to limit windup
float prev_err    = 0; // Previous error calculation storage

struct {
    unsigned int TC_read  : 1; // Interrupt flag for TC read
    unsigned int disp_ref : 1; // Interrupt flag for display refresh
    unsigned int disp_dig : 1; // Display digit tracker
} flags;

// Read from SPI slave
uint8_t SPI_read(void);

// Shift out to SPI line
void SPI_out(uint8_t dat);

// Print value to UART
void char_print(uint8_t dat);

// Enter data in buffer
void buff_put(uint16_t dat);

// Temperature display refresh
void ref_disp(void);

// Update display
void upd_disp(float dat);

// Read and store thermocouple data
uint16_t read_TC(void);

// Get average temperature
float get_avg_temp(void);

// Set PWM
void set_PWM(uint16_t PWM);

// Update PWM
void upd_PWM(void);

void init(void);


#endif	/* DOUGH_GO_8BIT_H */

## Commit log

2024-12-22 Initial DoughGo project
2024-12-22 Fix double calculation check for cur_PWM
2024-12-22 Changed to vars to floats
2024-12-23 Fix set temperature
2024-12-23 Fix double calculation of PWM
2024-12-23 Remove integral term & modify proportional gain
2024-12-23 Compartmentalize 8bit functionality
